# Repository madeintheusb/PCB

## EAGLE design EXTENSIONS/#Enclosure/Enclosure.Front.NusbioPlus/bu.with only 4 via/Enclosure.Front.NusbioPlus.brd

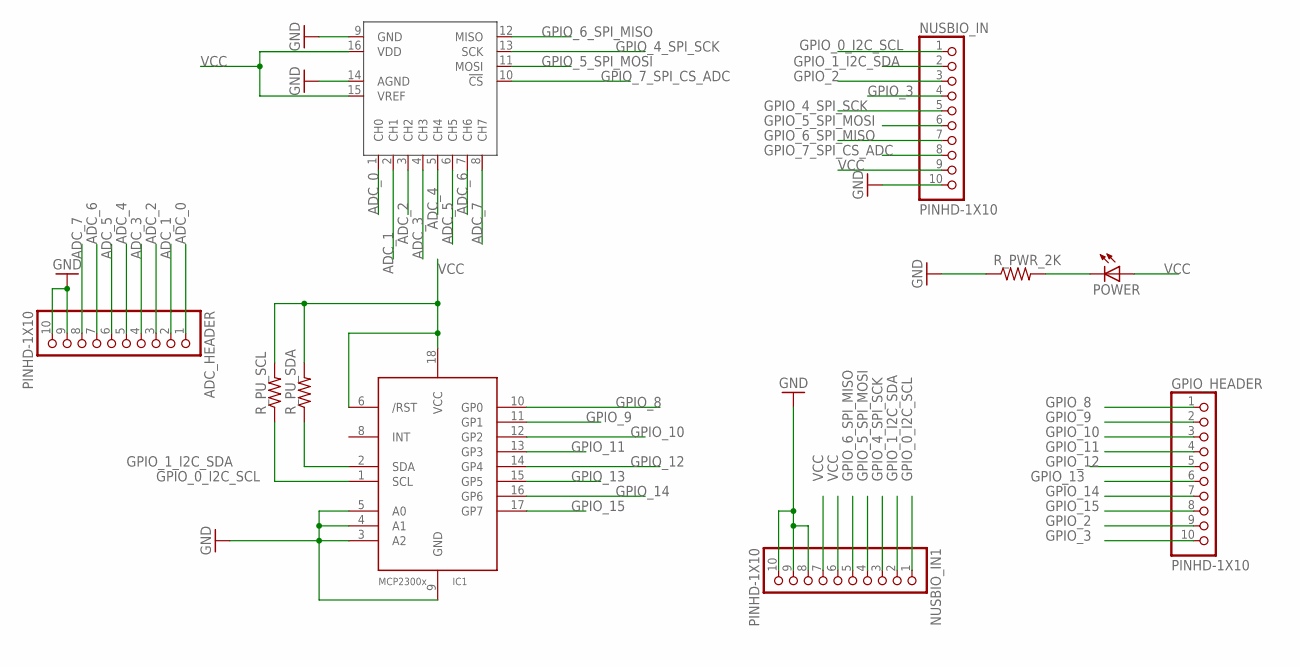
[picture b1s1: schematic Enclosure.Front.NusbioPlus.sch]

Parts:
ADC_HEADER: PINHD-1X10; 1X10-BIG
GPIO_HEADER: PINHD-1X10; 1X10-BIG
IC1: MCP23008/SO; SO18W
NUSBIO_IN, NUSBIO_IN1: PINHD-1X10; 1X10-BIG
POWER: LEDSMT1206; 1206
R_PU_SCL: R-US_R1206; R1206
R_PU_SDA: R-US_R1206; R1206
R_PWR_2K: R-US_R1206; R1206
U$1: MCP3008SL; SO16

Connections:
ADC_0: ADC_HEADER.1, U$1.1 (CH0)
ADC_1: ADC_HEADER.2, U$1.2 (CH1)
ADC_2: ADC_HEADER.3, U$1.3 (CH2)
ADC_3: ADC_HEADER.4, U$1.4 (CH3)
ADC_4: ADC_HEADER.5, U$1.5 (CH4)
ADC_5: ADC_HEADER.6, U$1.6 (CH5)
ADC_6: ADC_HEADER.7, U$1.7 (CH6)
ADC_7: ADC_HEADER.8, U$1.8 (CH7)
GND: ADC_HEADER.9, ADC_HEADER.10, IC1.3 (A2), IC1.4 (A1), IC1.5 (A0), IC1.9 (GND), NUSBIO_IN.10, NUSBIO_IN1.8, NUSBIO_IN1.9, NUSBIO_IN1.10, R_PWR_2K.1, U$1.9 (GND), U$1.14 (AGND)
GPIO_0_I2C_SCL: IC1.1 (SCL), NUSBIO_IN.1, NUSBIO_IN1.1, R_PU_SCL.1
GPIO_1_I2C_SDA: IC1.2 (SDA), NUSBIO_IN.2, NUSBIO_IN1.2, R_PU_SDA.1
GPIO_2: GPIO_HEADER.9, NUSBIO_IN.3
GPIO_3: GPIO_HEADER.10, NUSBIO_IN.4
GPIO_4_SPI_SCK: NUSBIO_IN.5, NUSBIO_IN1.3, U$1.13 (SCK)
GPIO_5_SPI_MOSI: NUSBIO_IN.6, NUSBIO_IN1.4, U$1.11 (MOSI)
GPIO_6_SPI_MISO: NUSBIO_IN.7, NUSBIO_IN1.5, U$1.12 (MISO)
GPIO_7_SPI_CS_ADC: NUSBIO_IN.8, U$1.10 (!CS)
GPIO_8: GPIO_HEADER.1, IC1.10 (GP0)
GPIO_9: GPIO_HEADER.2, IC1.11 (GP1)
GPIO_10: GPIO_HEADER.3, IC1.12 (GP2)
GPIO_11: GPIO_HEADER.4, IC1.13 (GP3)
GPIO_12: GPIO_HEADER.5, IC1.14 (GP4)
GPIO_13: GPIO_HEADER.6, IC1.15 (GP5)
GPIO_14: GPIO_HEADER.7, IC1.16 (GP6)
GPIO_15: GPIO_HEADER.8, IC1.17 (GP7)
unnamed: POWER.C, R_PWR_2K.2
VCC: IC1.6 (/RST), IC1.18 (VCC), NUSBIO_IN.9, NUSBIO_IN1.6, NUSBIO_IN1.7, POWER.A, R_PU_SCL.2, R_PU_SDA.2, U$1.15 (VREF), U$1.16 (VDD)

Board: 2 copper layers, 10 parts (5 on the bottom side), 27 nets, no tracks yet.

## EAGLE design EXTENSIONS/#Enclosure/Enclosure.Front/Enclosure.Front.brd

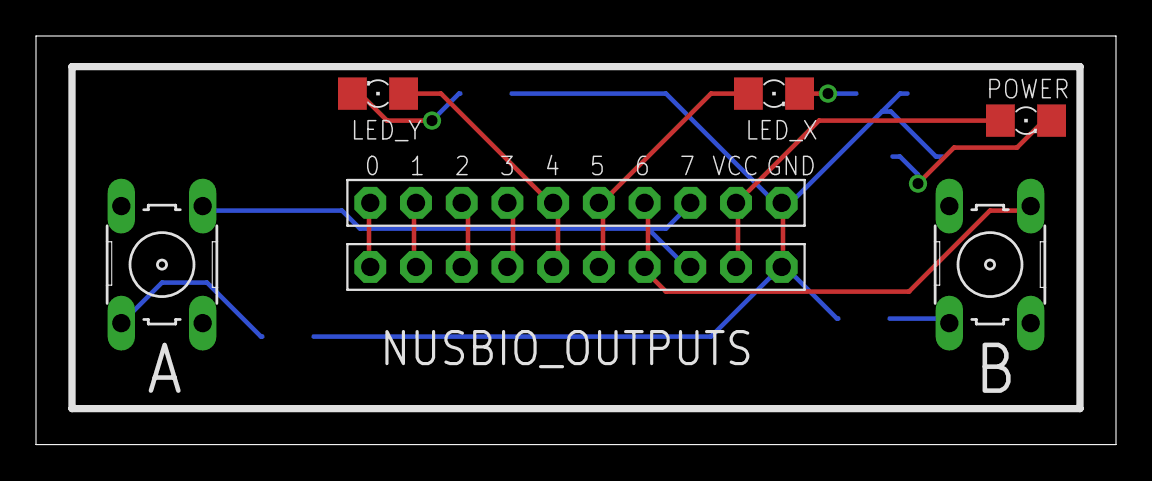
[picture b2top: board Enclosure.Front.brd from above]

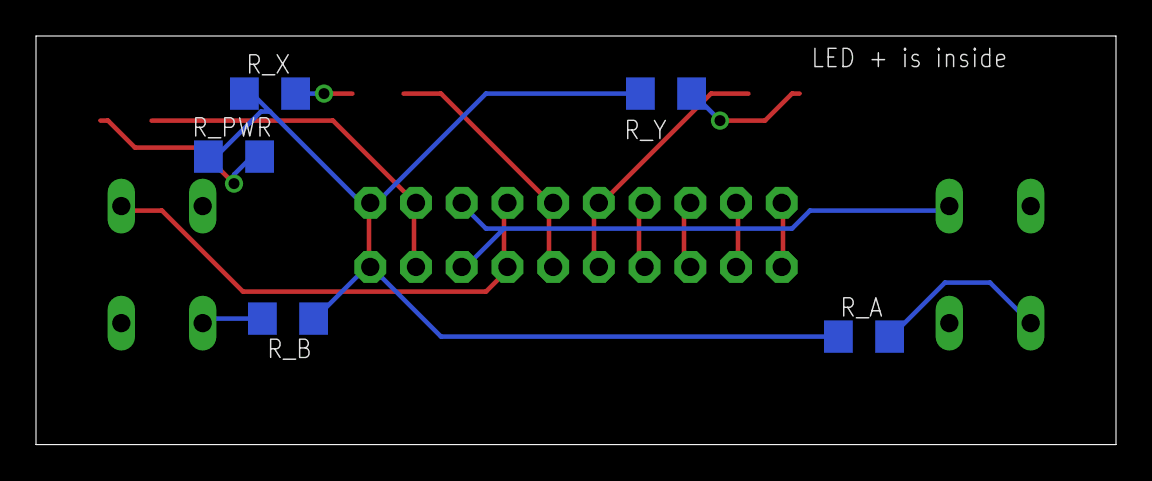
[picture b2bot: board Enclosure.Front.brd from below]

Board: 2 copper layers, 60.0 x 22.7 mm, 12 parts (5 on the bottom side), 15 nets.

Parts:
A: B3F-10XX
B: B3F-10XX
LED_X: 1206
LED_Y: 1206
NUSBIO_IN: PINHD-1X10; 1X10-BIG
NUSBIO_OUTPUTS: PINHD-1X10; 1X10-BIG
POWER: 1206
R_A: R1206
R_B: R1206
R_PWR: R1206
R_X: R1206
R_Y: R1206

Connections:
GND: NUSBIO_IN.10, NUSBIO_OUTPUTS.10, R_A.1, R_B.1, R_PWR.1, R_X.1, R_Y.1
GPIO_0: NUSBIO_IN.1, NUSBIO_OUTPUTS.1
GPIO_1: NUSBIO_IN.2, NUSBIO_OUTPUTS.2
GPIO_2: NUSBIO_IN.3, NUSBIO_OUTPUTS.3
GPIO_3: NUSBIO_IN.4, NUSBIO_OUTPUTS.4
GPIO_4: LED_Y.A, NUSBIO_IN.5, NUSBIO_OUTPUTS.5
GPIO_5: LED_X.A, NUSBIO_IN.6, NUSBIO_OUTPUTS.6
GPIO_6: B.1, NUSBIO_IN.7, NUSBIO_OUTPUTS.7
GPIO_7: A.1, NUSBIO_IN.8, NUSBIO_OUTPUTS.8
unnamed: POWER.C, R_PWR.2
unnamed: A.4, R_A.2
unnamed: B.4, R_B.2
unnamed: LED_X.C, R_X.2
unnamed: LED_Y.C, R_Y.2
VCC: NUSBIO_IN.9, NUSBIO_OUTPUTS.9, POWER.A

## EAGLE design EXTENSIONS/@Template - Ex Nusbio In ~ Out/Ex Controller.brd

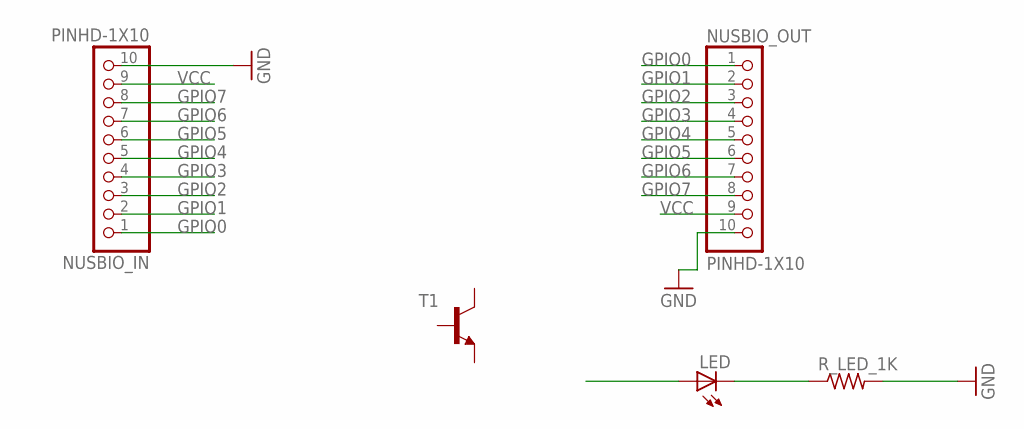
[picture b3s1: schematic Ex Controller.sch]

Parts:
LED: LEDCHIPLED_0805; CHIPLED_0805
NUSBIO_IN: PINHD-1X10; 1X10-BIG
NUSBIO_OUT: PINHD-1X10; 1X10-BIG
R_LED_1K: R-US_R0805; R0805
T1: MMBT3904LT1-NPN-SOT23-BEC; SOT23-BEC

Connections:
GND: NUSBIO_IN.10, NUSBIO_OUT.10, R_LED_1K.2
GPIO0: NUSBIO_IN.1, NUSBIO_OUT.1
GPIO1: NUSBIO_IN.2, NUSBIO_OUT.2
GPIO2: NUSBIO_IN.3, NUSBIO_OUT.3
GPIO3: NUSBIO_IN.4, NUSBIO_OUT.4
GPIO4: NUSBIO_IN.5, NUSBIO_OUT.5
GPIO5: NUSBIO_IN.6, NUSBIO_OUT.6
GPIO6: NUSBIO_IN.7, NUSBIO_OUT.7
GPIO7: NUSBIO_IN.8, NUSBIO_OUT.8
unnamed: LED.C, R_LED_1K.1
VCC: NUSBIO_IN.9, NUSBIO_OUT.9

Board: 2 copper layers, 5 parts (0 on the bottom side), 11 nets, no tracks yet.

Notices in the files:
parts and their libraries:
SparkFun-Aesthetics: Licensing: Creative Commons ShareAlike 4.0 International - https://creativecommons.org/licenses/by-sa/4.0
